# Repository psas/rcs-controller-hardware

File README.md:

# rcs-controller-hardware
The controller PCB for the RCS v2 module

Design documentation can be found [here](https://docs.google.com/document/d/1iXMG_Qmra7nCvFc8n4LBztUYELcxyuHCIxhkm7w4VaU/edit?usp=sharing).
## LICENSE

Copyright the Portland State Aerospace Society, 2025.

This source describes Open Hardware that is licensed under CERN-OHL-S v2, or any later version.

You may redistribute and modify this source and make products using it under the terms of the CERN-OHL-S v2 (https://ohwr.org/cern_ohl_s_v2.txt).

This source is distributed WITHOUT ANY EXPRESS OR IMPLIED WARRANTY, INCLUDING OF MERCHANTABILITY, SATISFACTORY QUALITY AND FITNESS FOR A PARTICULAR PURPOSE. Please see the CERN-OHL-S v2 for applicable conditions.

Source location: https://github.com/psas/

If you require a different license for this open hardware project, please contact us at [aerospace@pdx.edu](mailto:aerospace@pdx.edu).

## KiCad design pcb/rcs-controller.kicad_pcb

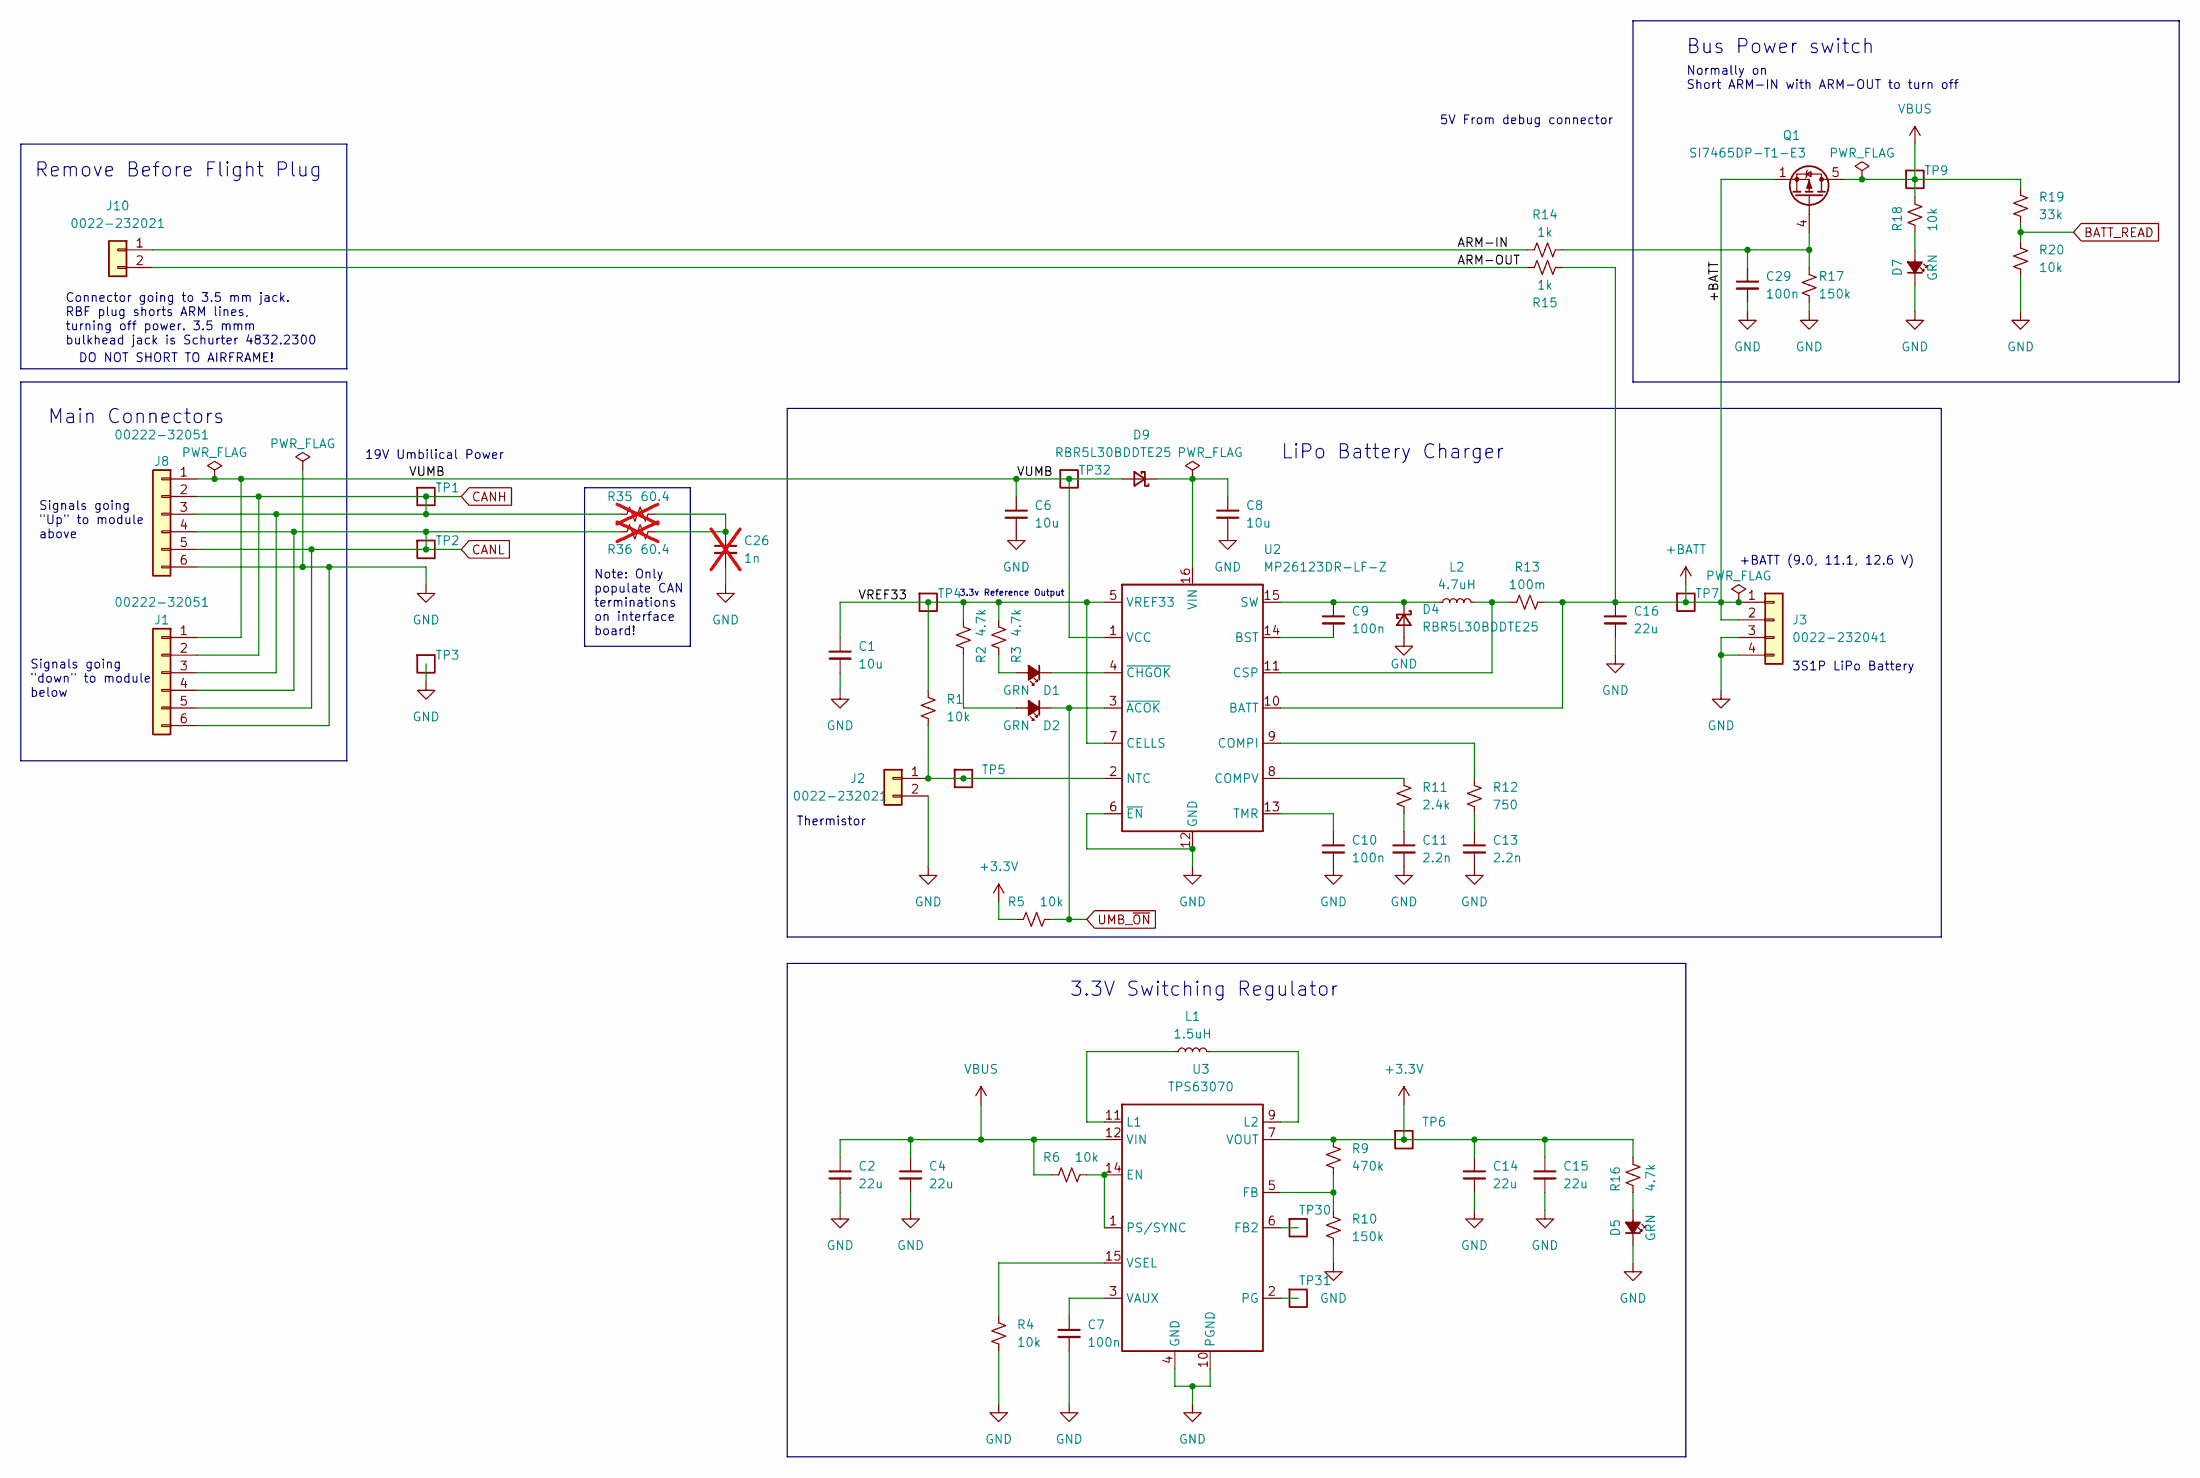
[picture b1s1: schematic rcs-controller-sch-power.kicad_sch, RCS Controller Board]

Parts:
C1, C6, C8: 10u; C_0805_2012Metric; MPN GRM21BR61H106KE43L
C2, C4, C14, C15, C16: 22u; C_0805_2012Metric; MPN C2012X5R1V226M125AC
C7, C9, C10, C29: 100n; C_0603_1608Metric; MPN CL10B104KB8WPNC
C11, C13: 2.2n; C_0603_1608Metric; MPN CL10B222KB8WPNC
C26: 1n; C_0603_1608Metric; MPN CL10B102KB85PNL; not fitted
D1, D2, D5, D7: GRN; LED_0603_1608Metric; MPN 150060GS75000
D4, D9: RBR5L30BDDTE25; D_SMA; MPN RBR5L30BDDTE25
J1, J8: 00222-32051; Molex_KK-254_AE-6410-06A_1x06_P2.54mm_Vertical; MPN 22232061
J2, J10: 0022-232021; Molex_KK-254_AE-6410-02A_1x02_P2.54mm_Vertical; MPN 22232021
J3: 0022-232041; Molex_KK-254_AE-6410-04A_1x04_P2.54mm_Vertical; MPN 22232041
L1: 1.5uH; L_Vishay_IHLP-2020; MPN IHLP2020CZER1R5M11
L2: 4.7uH; L_Vishay_IHLP-2020; MPN IHLP2020BZER4R7M11
Q1: SI7465DP-T1-E3; PowerPAK_SO-8_Single; MPN SI7141DP-T1-GE3
R1, R4, R5, R6, R18, R20: 10k; R_0603_1608Metric; MPN RC0603FR-0710KL
R2, R3, R16: 4.7k; R_0603_1608Metric; MPN RC0603FR-074K7L
R9: 470k; R_0603_1608Metric; MPN RC0603FR-07470KL
R10, R17: 150k; R_0603_1608Metric; MPN RC0603FR-07150KL
R11: 2.4k; R_0603_1608Metric; MPN RC0603FR-072K4L
R12: 750; R_0603_1608Metric; MPN RC0603FR-07750RL
R13: 100m; R_1206_3216Metric; MPN CSR1206FTR100
R14, R15: 1k; R_0603_1608Metric; MPN RC0603FR-071KL
R19: 33k; R_0603_1608Metric; MPN RC0603FR-0733KL
R35, R36: 60.4; R_1206_3216Metric; MPN RC0603FR-0760R4L; not fitted
TP1, TP2, TP3, TP4, TP5, TP6, TP7, TP9, TP30, TP31, TP32: Test-Point; TP-through-hole-1X01
U2: MP26123DR-LF-Z; QFN-16-1EP_4x4mm_P0.65mm_EP2.5x2.5mm; MPN MP26123DR-LF-Z
U3: TPS63070; U-TI-TPS63070; MPN TPS63070RNMR

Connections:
+3.3V: C14.1, C15.1, R5.1, R9.1, R16.1, TP6.1, U3.7 (VOUT), U3.8 (VOUT), U3.TIE2 (VOUT); also elsewhere on the board
+BATT: C16.1, J3.1, J3.2, Q1.1 (S), Q1.2 (S), Q1.3 (S), R13.2, R15.1, TP7.1, U2.10 (BATT)
/Power/ARM-IN: J10.1, R14.1
/Power/ARM-OUT: J10.2, R15.2
/Power/VREF33: C1.1, R1.1, R2.1, R3.1, TP4.1, U2.5 (VREF33), U2.7 (CELLS)
/Power/VUMB: C6.1, D9.2 (A), J1.1, J8.1, TP32.1, U2.1 (VCC)
BATT_READ: R19.2, R20.1; also elsewhere on the board
CANH: J1.2, J1.3, J8.2, J8.3, R35.1, TP1.1
CANL: J1.4, J1.5, J8.4, J8.5, R36.2, TP2.1
GND: C1.2, C2.2, C4.2, C6.2, C7.2, C8.2, C10.2, C11.2, C13.2, C14.2, C15.2, C16.2, C26.2, C29.2, D4.2 (A), D5.1 (K), D7.1 (K), J1.6, J2.2, J3.3, J3.4, J8.6, R4.2, R10.2, R17.2, R20.2, TP3.1, U2.6 (~EN), U2.12 (GND), U2.17 (GND), U3.4 (GND), U3.10 (PGND); also elsewhere on the board
unnamed: C11.1, R11.2
unnamed: C13.1, R12.2
unnamed: C26.1, R35.2, R36.1
unnamed: D1.2 (A), R3.2
unnamed: D1.1 (K), U2.4 (~CHGOK)
unnamed: D2.2 (A), R2.2
unnamed: C9.1, D4.1 (K), L2.1, U2.15 (SW)
unnamed: D5.2 (A), R16.2
unnamed: D7.2 (A), R18.2
unnamed: C8.1, D9.1 (K), U2.16 (VIN)
unnamed: J2.1, R1.2, TP5.1, U2.2 (NTC)
unnamed: C29.1, Q1.4 (G), R14.2, R17.1
unnamed: C9.2, U2.14 (BST)
unnamed: R12.1, U2.9 (COMPI)
unnamed: R11.1, U2.8 (COMPV)
unnamed: L2.2, R13.1, U2.11 (CSP)
unnamed: C10.1, U2.13 (TMR)
unnamed: R6.2, U3.1 (PS/SYNC), U3.14 (EN)
unnamed: TP30.1, U3.6 (FB2)
unnamed: R9.2, R10.1, U3.5 (FB)
unnamed: L1.1, U3.11 (L1)
unnamed: L1.2, U3.9 (L2)
unnamed: TP31.1, U3.2 (PG)
unnamed: C7.1, U3.3 (VAUX)
unnamed: R4.1, U3.15 (VSEL)
UMB_~ON: D2.1 (K), R5.2, U2.3 (~ACOK); also elsewhere on the board
VBUS: C2.1, C4.1, Q1.5 (D), R6.1, R18.1, R19.1, TP9.1, U3.12 (VIN), U3.13 (VIN), U3.TIE1 (VIN); also elsewhere on the board

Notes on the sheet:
LiPo Battery Charger
DO NOT SHORT TO AIRFRAME!
Thermistor
Signals going "down" to module below
Normally on Short ARM-IN with ARM-OUT to turn off
Connector going to 3.5 mm jack. RBF plug shorts ARM lines, turning off power. 3.5 mmm bulkhead jack is Schurter 4832.2300
Note: Only populate CAN terminations on interface board!
3S1P LiPo Battery
Signals going "Up" to module above
19V Umbilical Power
+BATT (9.0, 11.1, 12.6 V)
Bus Power switch
Main Connectors
3.3V Switching Regulator
5V From debug connector
3.3v Reference Output
Remove Before Flight Plug

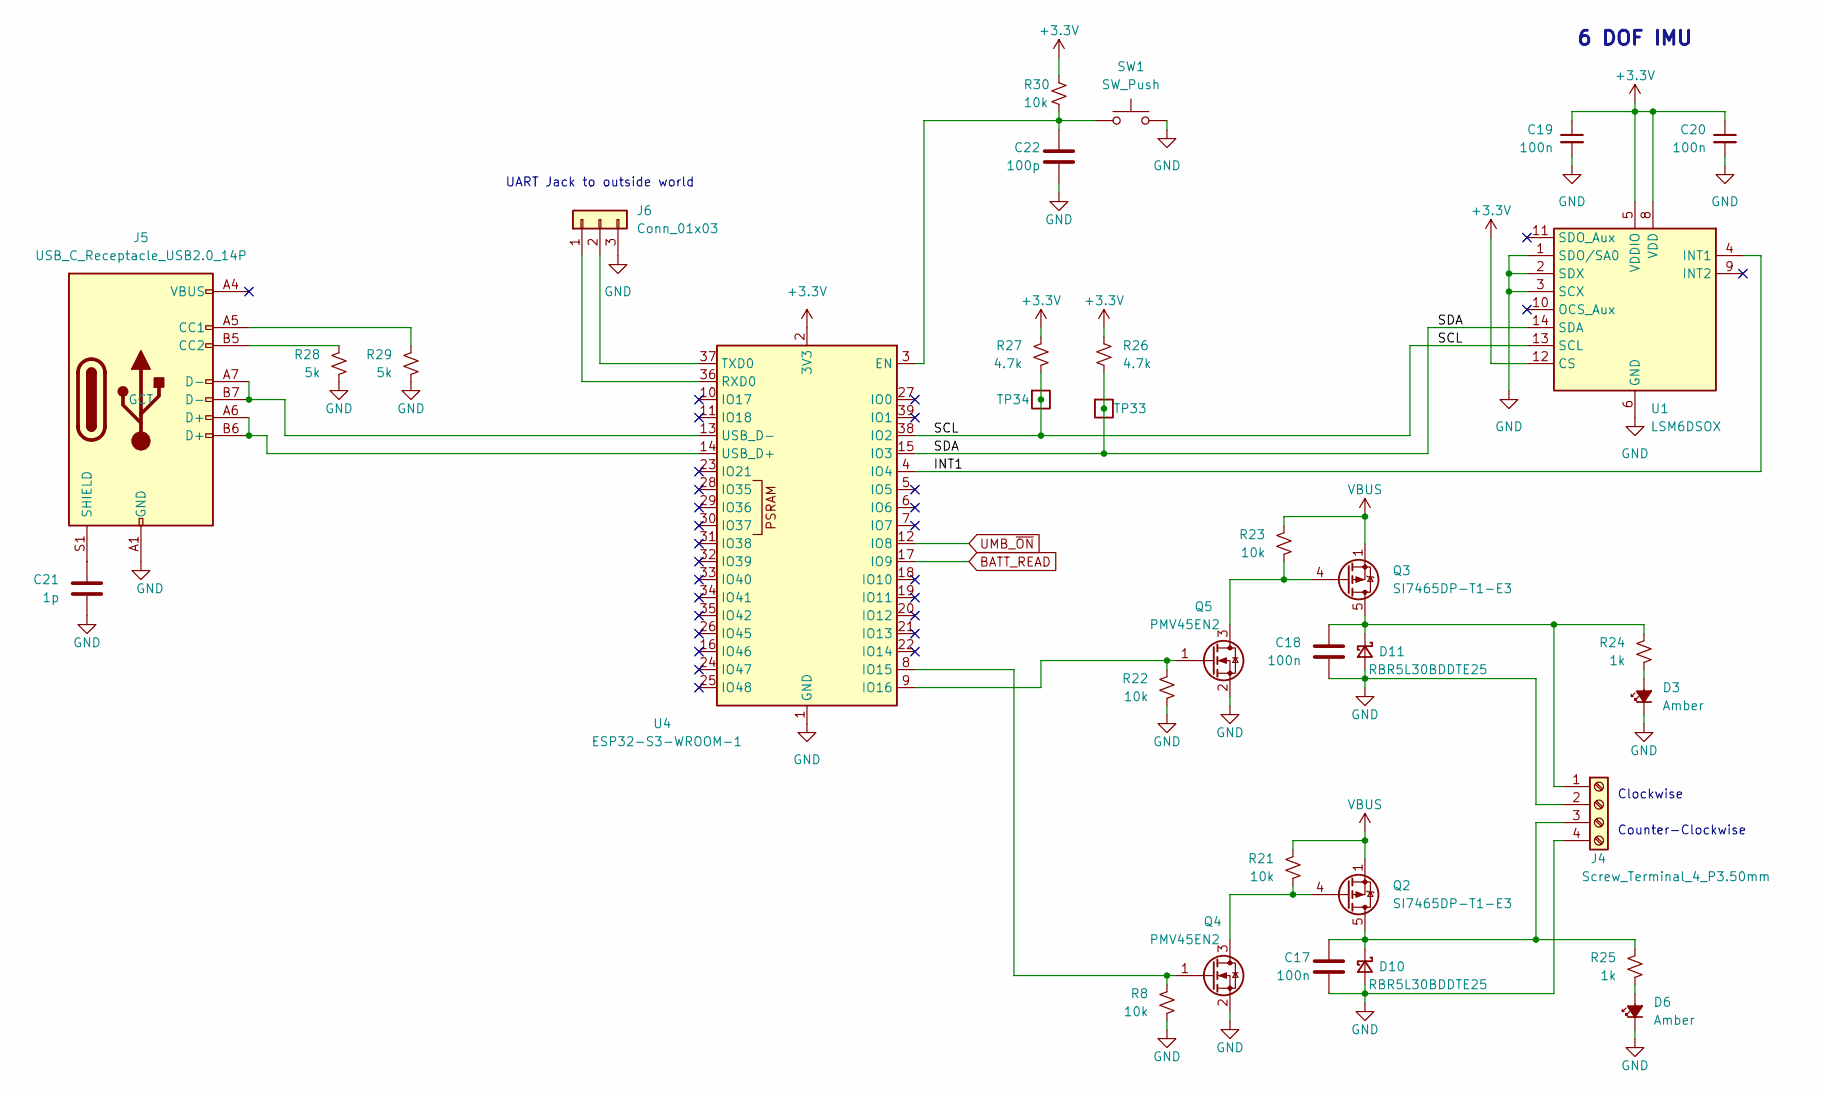
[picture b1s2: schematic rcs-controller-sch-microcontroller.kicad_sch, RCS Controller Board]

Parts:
C17, C18, C19, C20: 100n; C_0603_1608Metric; MPN CL10B104KB8WPNC
C21: 1p; C_0603_1608Metric; MPN CL10B104KB8WPNC
C22: 100p; C_0603_1608Metric; MPN CL10B104KB8WPNC
D3, D6: Amber; LED_0603_1608Metric; MPN 150060YS75000
D10, D11: RBR5L30BDDTE25; D_SMA; MPN RBR5L30BDDTE25
J4: Screw_Terminal_4_P3.50mm; TerminalBlock_Phoenix_PT-1,5-4-3.5-H_1x04_P3.50mm_Horizontal; MPN 1751264
J5: USB_C_Receptacle_USB2.0_14P; USB_C_Receptacle_Palconn_UTC16-G; MPN USB4105-GF-A
J6: Conn_01x03; PinHeader_1x03_P2.54mm_Vertical
Q2, Q3: SI7465DP-T1-E3; PowerPAK_SO-8_Single; MPN SI7141DP-T1-GE3
Q4, Q5: PMV45EN2; SOT-23-3; MPN PMV45EN2R
R8, R21, R22, R23, R30: 10k; R_0603_1608Metric; MPN RC0603FR-0710KL
R24, R25: 1k; R_0603_1608Metric; MPN RC0603FR-071KL
R26, R27: 4.7k; R_0603_1608Metric; MPN RC0603FR-074K7L
R28, R29: 5k; R_0603_1608Metric; MPN RC0603FR-0710KL
SW1: SW_Push; SW_PUSH_6mm; MPN B3F-1000
TP33, TP34: Test-Point; TP-through-hole-1X01
U1: LSM6DSOX; LGA-14_3x2.5mm_P0.5mm_LayoutBorder3x4y; MPN LSM6DSOXTR
U4: ESP32-S3-WROOM-1; MPN ESP32-S3-WROOM-1-N4R8

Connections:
+3.3V: C19.1, C20.1, R26.1, R27.1, R30.1, U1.5 (VDDIO), U1.8 (VDD), U1.12 (CS), U4.2 (3V3); also elsewhere on the board
/Microcontroller/INT1: U1.4 (INT1), U4.4 (IO4)
/Microcontroller/SCL: R27.2, TP34.1, U1.13 (SCL), U4.38 (IO2)
/Microcontroller/SDA: R26.2, TP33.1, U1.14 (SDA), U4.15 (IO3)
BATT_READ: U4.17 (IO9); also elsewhere on the board
GND: C17.2, C18.2, C19.2, C20.2, C21.2, C22.2, D3.1 (K), D6.1 (K), D10.2 (A), D11.2 (A), J4.2, J4.4, J5.A1 (GND), J5.A12 (GND), J5.B1 (GND), J5.B12 (GND), J6.3, Q4.2 (S), Q5.2 (S), R8.2, R22.2, R28.2, R29.2, SW1.2, U1.1 (SDO/SA0), U1.2 (SDX), U1.3 (SCX), U1.6 (GND), U1.7 (GND), U4.1 (GND), U4.40 (GND), U4.41 (GND); also elsewhere on the board
unnamed: D3.2 (A), R24.2
unnamed: D6.2 (A), R25.2
unnamed: C17.1, D10.1 (K), J4.3, Q2.5 (D), R25.1
unnamed: C18.1, D11.1 (K), J4.1, Q3.5 (D), R24.1
unnamed: J5.A5 (CC1), R29.1
unnamed: J5.B5 (CC2), R28.1
unnamed: C21.1, J5.S1 (SHIELD)
unnamed: J6.1, U4.36 (RXD0)
unnamed: J6.2, U4.37 (TXD0)
unnamed: Q2.4 (G), Q4.3 (D), R21.2
unnamed: Q3.4 (G), Q5.3 (D), R23.2
unnamed: Q4.1 (G), R8.1, U4.8 (IO15)
unnamed: Q5.1 (G), R22.1, U4.9 (IO16)
unnamed: C22.1, R30.2, SW1.1, U4.3 (EN)
unnamed: J5.A6 (D+), J5.B6 (D+), U4.14 (USB_D+)
unnamed: J5.A7 (D-), J5.B7 (D-), U4.13 (USB_D-)
UMB_~ON: U4.12 (IO8); also elsewhere on the board
VBUS: Q2.1 (S), Q2.2 (S), Q2.3 (S), Q3.1 (S), Q3.2 (S), Q3.3 (S), R21.1, R23.1; also elsewhere on the board

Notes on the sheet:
Counter-Clockwise
Clockwise
6 DOF IMU
UART Jack to outside world

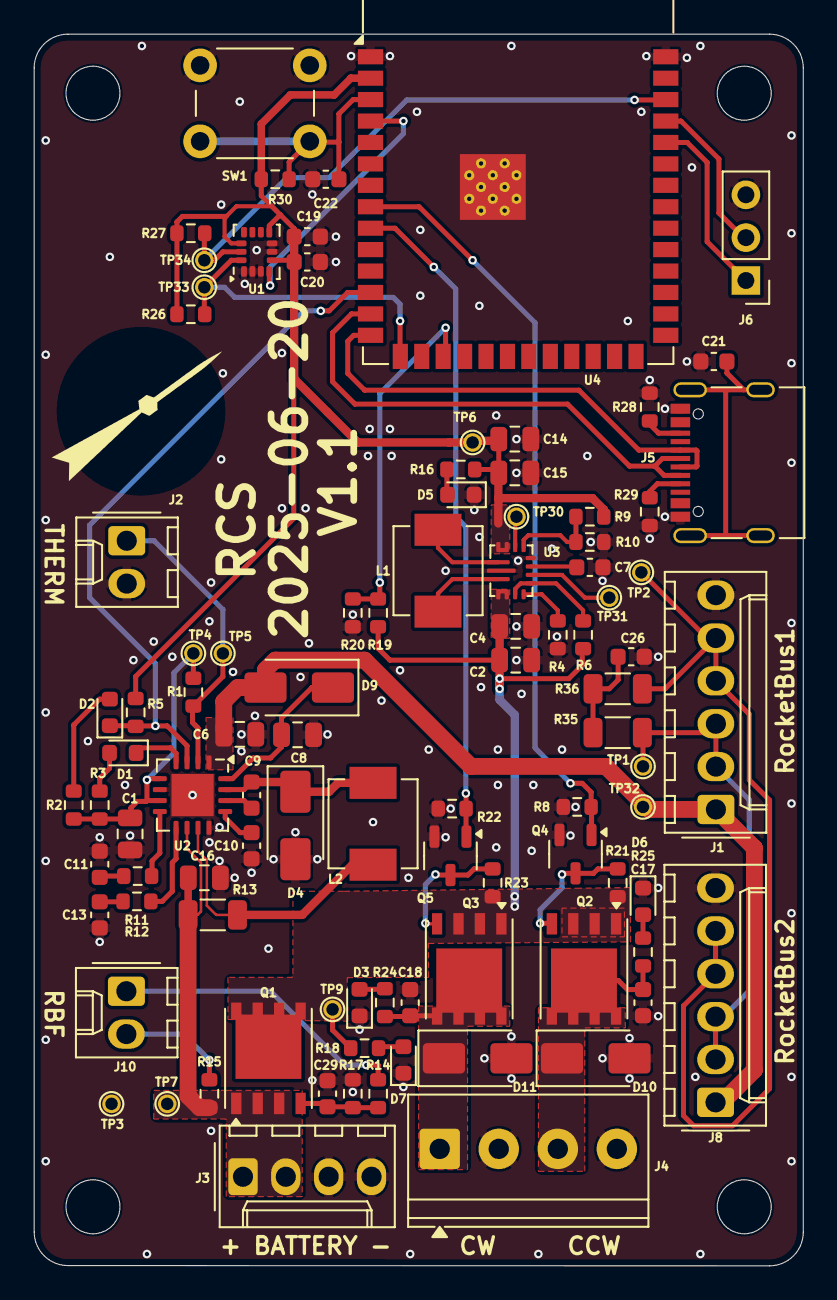
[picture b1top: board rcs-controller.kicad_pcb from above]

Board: 2 copper layers, 45.6 x 73.0 mm, 96 parts (0 on the bottom side), 56 nets.

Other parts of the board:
LOGO1: PSAS_LOGO_10X10

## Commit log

2025-03-10 first commit of kicad files
2025-03-10 updated library paths
2025-03-24 Upload of rcs controller board 1st draft
2025-03-31 Updated with footprint and more fleshed out circuit
2025-04-02 Rough draft schematic, no ERC errors, ready for layout
2025-04-02 remove temporary and lock files that were somehow committed; rename schematic files to something sane.
2025-04-02 First circuit board
2025-04-02 Added some directories to gitignore, and removed another temp files.
2025-04-10 Push to move to other machine
2025-04-14 Rev2
2025-04-24 Submit for review 4.23.2025
2025-04-25 Rev for review 4.25.2025
2025-04-28 Cleanup of Jacob's board; mostly ready for fab
2025-04-30 Fixed BOM, fixed missing symbol and footprint libraries, stitched vias, generated Gerbers.
2025-05-14 Added iBOM for easier board stuffing
2025-05-29 Rev 2.0
    Updated board with ESP32 chip to replace feather
2025-06-03 Revision 6/2
2025-06-04 Design review; fix schematic issues and some polish, some board to schematic patching, fix footprint issues.
2025-06-16 Rev date 6.15
2025-06-16 rev date 6.16.2025
2025-06-18 Cleaner board
2025-06-18 Rev. 6.17
2025-06-19 Board design review; fix DRC errors. Back to Jacob for polishing.
2025-06-19 Silkscreen clean up
2025-06-20 More DRC cleanup, polishing, sticthing. Should be good to go.
2025-06-20 Oh, right, update the version and date.
2025-06-23 more polish, build Gerbers
2025-06-24 Push for design review 6.24
